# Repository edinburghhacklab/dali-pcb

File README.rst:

DALI PCB
========

Overview
--------

PCB to power and interface with DALI using an ESP32-S3.

Dimensions: 100mm W × 75mm H

Usage
-----

This is a KiCad project.

* `Software <https://github.com/edinburghhacklab/mqtt-dali-controller>`_

Schematics
----------

Power for the DALI bus is optional and can be connected using the solder jumper
bridges. If the power is supplied by this PCB then the polarity of the bus is
fixed so the bridge rectifier can be omitted.

.. image:: render/Root-sch.svg
   :alt: Root schematic

DALI
~~~~

There are 2 DALI bus connections.

.. image:: render/DALI-sch.svg
   :alt: DALI schematic

Power
~~~~~

Power for the DALI bus is supplied by an external 12-22V DC power supply. Power
for the microcontroller is supplied by USB to the development board or an
external 5V DC power supply.

.. image:: render/Power-sch.svg
   :alt: Power schematic

Microcontroller
~~~~~~~~~~~~~~~

Connect a `LOLIN S3  <https://www.wemos.cc/en/latest/s3/s3.html>`_ development
board to the pin sockets.

.. image:: render/Microcontroller-sch.svg
   :alt: Microcontroller schematic

I/O
~~~

Analogue and digital I/O pin headers are provided for integrations with external
switches and rotary encoders.

The DALI bus also has a 3.3V direct pin header which can only be used when the
microcontroller is disconnected. This can't be used with a standard UART because
the DALI communication uses Manchester (bi-phase) encoding.

.. image:: render/IO-sch.svg
   :alt: I/O schematic

PCB
---

* Internal bus power: populate JP1-2, and populate either JP3-4 or D5
* External bus power: populate D5, do not populate JP1-4

.. image:: render/DALI-pcb.svg
   :alt: DALI PCB

Components
----------

+---------------------+----------+--------------------------------------------------------+
| Refs                | Quantity | Name                                                   |
+=====================+==========+========================================================+
|                     |     1    | LOLIN S3 Development Board                             |
+---------------------+----------+--------------------------------------------------------+
| D3                  |     1    | Diodes BAV99-7-F Dual Switching Diode, SOT-23-3        |
+---------------------+----------+--------------------------------------------------------+
| D4                  |     1    | Diodes DDZ9689S-7 Zener Diode, SOD-323                 |
+---------------------+----------+--------------------------------------------------------+
| D5                  |     1    | Infineon BGX50AE6327 Diode Bridge, SOT-143             |
+---------------------+----------+--------------------------------------------------------+
| J1, J2, J3, J4      |     4    | 1x02 Terminal Block, Through Hole (5.08mm)             |
+---------------------+----------+--------------------------------------------------------+
| J5, J6              |     2    | 1x20 Pin Socket, Through Hole (2.54mm)                 |
+---------------------+----------+--------------------------------------------------------+
| J7                  |     1    | 1x04 Pin Header, Through Hole (2.54mm)                 |
+---------------------+----------+--------------------------------------------------------+
| J8, J9              |     2    | 2x13 Pin Header, Through Hole (2.54mm)                 |
+---------------------+----------+--------------------------------------------------------+
| Q1                  |     1    | ON Semiconductor PZT2222AT1G NPN Transistor, SOT-223   |
+---------------------+----------+--------------------------------------------------------+
| Q2                  |     1    | ON Semiconductor MMBT2222ALT1G NPN Transistor, SOT-23  |
+---------------------+----------+--------------------------------------------------------+
| R2                  |     1    | 12Ω 1W Resistor, SMD 2512 (Metric 6332)                |
+---------------------+----------+--------------------------------------------------------+
| R3, R8              |     2    | 1kΩ 1W Resistor, SMD 2512 (Metric 6332)                |
+---------------------+----------+--------------------------------------------------------+
| R4                  |     1    | 120Ω 125mW Resistor, SMD 0805 (Metric 2012)            |
+---------------------+----------+--------------------------------------------------------+
| R5                  |     1    | 220Ω 125mW Resistor, SMD 0805 (Metric 2012)            |
+---------------------+----------+--------------------------------------------------------+
| R6                  |     1    | 2.2kΩ 250mW Resistor, SMD 1206 (Metric 3216)           |
+---------------------+----------+--------------------------------------------------------+
| R7                  |     1    | 10kΩ 125mW Resistor, SMD 0805 (Metric 2012)            |
+---------------------+----------+--------------------------------------------------------+
| U1, U2              |     2    | Vishay Semiconductors TCLT1000 Optocoupler, SOP-4L     |
+---------------------+----------+--------------------------------------------------------+

Total pin header count: 56

References
----------

* `Digitally Addressable Lighting Interface (DALI) Communication <https://ww1.microchip.com/downloads/en/AppNotes/01465A.pdf>`_

* `Digitally Addressable Lighting Interface (DALI) Unit Using the MC68HC908KX8 <https://www.nxp.com/docs/en/reference-manual/DRM004.pdf>`_

* `Digital Addressable Lighting Interface (DALI) Implementation Using MSP430 Value Line Microcontrollers <https://www.ti.com/lit/an/slaa422a/slaa422a.pdf>`_

* `DALI Communication Using the EFR32 <https://www.silabs.com/documents/public/application-notes/an1220-efr32-dali.pdf>`_

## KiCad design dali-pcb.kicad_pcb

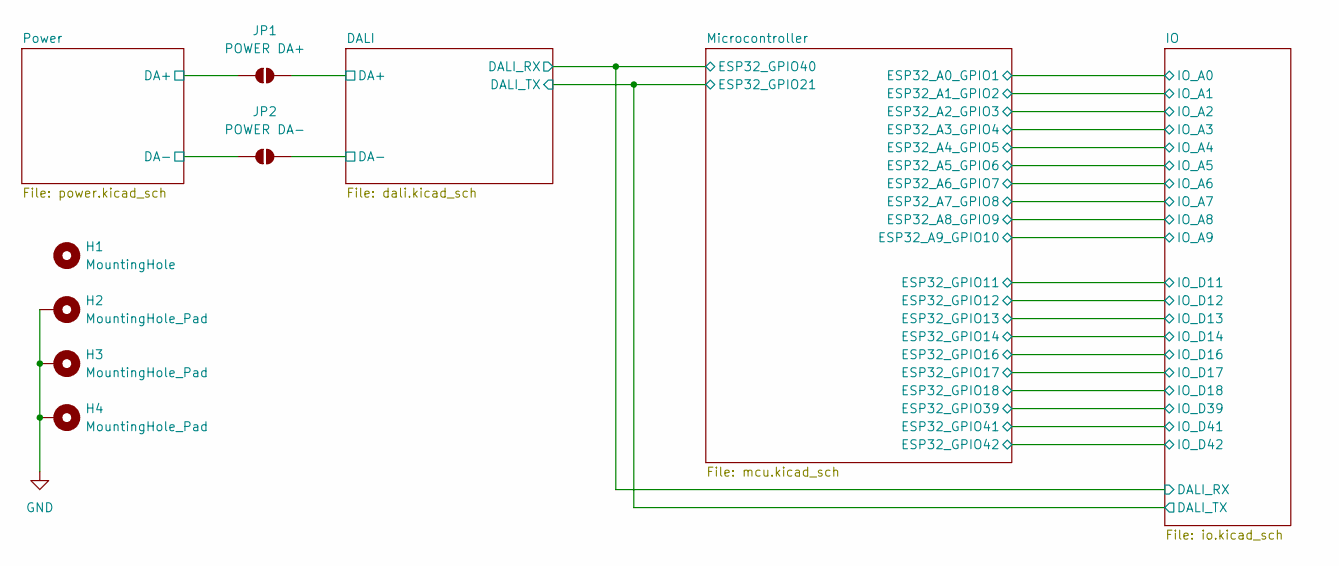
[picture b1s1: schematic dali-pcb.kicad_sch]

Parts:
H1: MountingHole; MountingHole_3.2mm_M3
H2, H3, H4: MountingHole_Pad; MountingHole_3.2mm_M3_Pad
JP1: POWER DA+; SolderJumper-2_P1.3mm_Open_RoundedPad1.0x1.5mm
JP2: POWER DA-; SolderJumper-2_P1.3mm_Open_RoundedPad1.0x1.5mm

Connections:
/DALI/DA+: JP1.1 (A); also elsewhere on the board
/DALI/DA-: JP2.2 (B); also elsewhere on the board
/Power/DA+: JP1.2 (B); also elsewhere on the board
/Power/DA-: JP2.1 (A); also elsewhere on the board
GND: H2.1, H3.1, H4.1; also elsewhere on the board

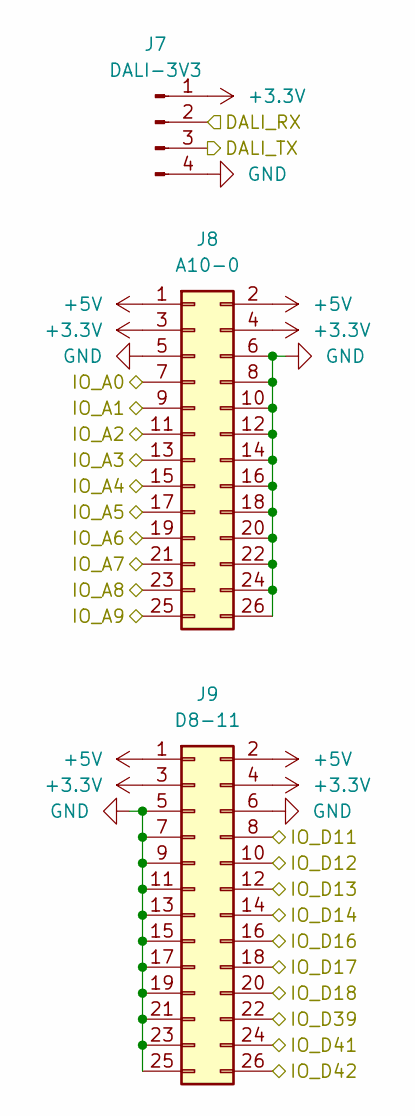
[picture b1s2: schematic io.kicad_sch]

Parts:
J7: DALI-3V3; PinHeader_1x04_P2.54mm_Vertical
J8: A10-0; PinHeader_2x13_P2.54mm_Vertical
J9: D8-11; PinHeader_2x13_P2.54mm_Vertical

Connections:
+3.3V: J7.1, J8.3, J8.4, J9.3, J9.4; also elsewhere on the board
+5V: J8.1, J8.2, J9.1, J9.2; also elsewhere on the board
/DALI/DALI_RX: J7.2; also elsewhere on the board
/DALI/DALI_TX: J7.3; also elsewhere on the board
/IO/IO_A0: J8.7; also elsewhere on the board
/IO/IO_A1: J8.9; also elsewhere on the board
/IO/IO_A2: J8.11; also elsewhere on the board
/IO/IO_A3: J8.13; also elsewhere on the board
/IO/IO_A4: J8.15; also elsewhere on the board
/IO/IO_A5: J8.17; also elsewhere on the board
/IO/IO_A6: J8.19; also elsewhere on the board
/IO/IO_A7: J8.21; also elsewhere on the board
/IO/IO_A8: J8.23; also elsewhere on the board
/IO/IO_A9: J8.25; also elsewhere on the board
/IO/IO_D11: J9.8; also elsewhere on the board
/IO/IO_D12: J9.10; also elsewhere on the board
/IO/IO_D13: J9.12; also elsewhere on the board
/IO/IO_D14: J9.14; also elsewhere on the board
/IO/IO_D16: J9.16; also elsewhere on the board
/IO/IO_D17: J9.18; also elsewhere on the board
/IO/IO_D18: J9.20; also elsewhere on the board
/IO/IO_D39: J9.22; also elsewhere on the board
/IO/IO_D41: J9.24; also elsewhere on the board
/IO/IO_D42: J9.26; also elsewhere on the board
GND: J7.4, J8.5, J8.6, J8.8, J8.10, J8.12, J8.14, J8.16, J8.18, J8.20, J8.22, J8.24, J8.26, J9.5, J9.6, J9.7, J9.9, J9.11, J9.13, J9.15, J9.17, J9.19, J9.21, J9.23, J9.25; also elsewhere on the board

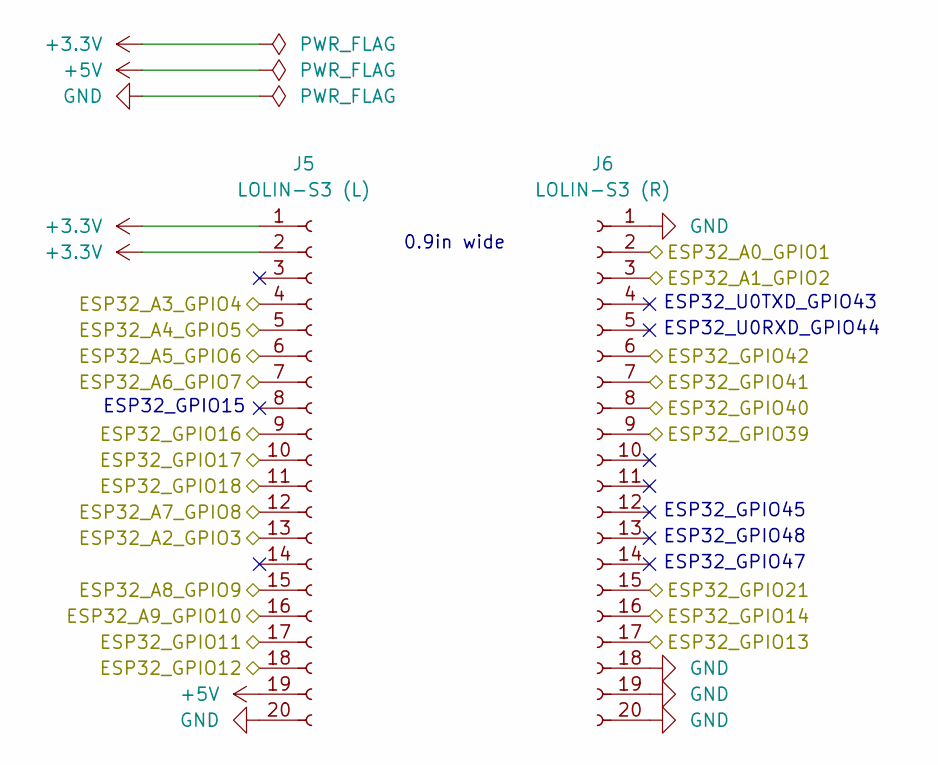
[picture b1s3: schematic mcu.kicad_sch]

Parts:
J5: LOLIN-S3 (L); PinSocket_1x20_P2.54mm_Vertical
J6: LOLIN-S3 (R); PinSocket_1x20_P2.54mm_Vertical

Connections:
+3.3V: J5.1, J5.2; also elsewhere on the board
+5V: J5.19; also elsewhere on the board
/DALI/DALI_RX: J6.8; also elsewhere on the board
/DALI/DALI_TX: J6.15; also elsewhere on the board
/IO/IO_A0: J6.2; also elsewhere on the board
/IO/IO_A1: J6.3; also elsewhere on the board
/IO/IO_A2: J5.13; also elsewhere on the board
/IO/IO_A3: J5.4; also elsewhere on the board
/IO/IO_A4: J5.5; also elsewhere on the board
/IO/IO_A5: J5.6; also elsewhere on the board
/IO/IO_A6: J5.7; also elsewhere on the board
/IO/IO_A7: J5.12; also elsewhere on the board
/IO/IO_A8: J5.15; also elsewhere on the board
/IO/IO_A9: J5.16; also elsewhere on the board
/IO/IO_D11: J5.17; also elsewhere on the board
/IO/IO_D12: J5.18; also elsewhere on the board
/IO/IO_D13: J6.17; also elsewhere on the board
/IO/IO_D14: J6.16; also elsewhere on the board
/IO/IO_D16: J5.9; also elsewhere on the board
/IO/IO_D17: J5.10; also elsewhere on the board
/IO/IO_D18: J5.11; also elsewhere on the board
/IO/IO_D39: J6.9; also elsewhere on the board
/IO/IO_D41: J6.7; also elsewhere on the board
/IO/IO_D42: J6.6; also elsewhere on the board
GND: J5.20, J6.1, J6.18, J6.19, J6.20; also elsewhere on the board

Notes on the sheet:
ESP32_U0TXD_GPIO43
ESP32_GPIO15
0.9in wide
ESP32_GPIO47
ESP32_GPIO45
ESP32_GPIO48
ESP32_U0RXD_GPIO44

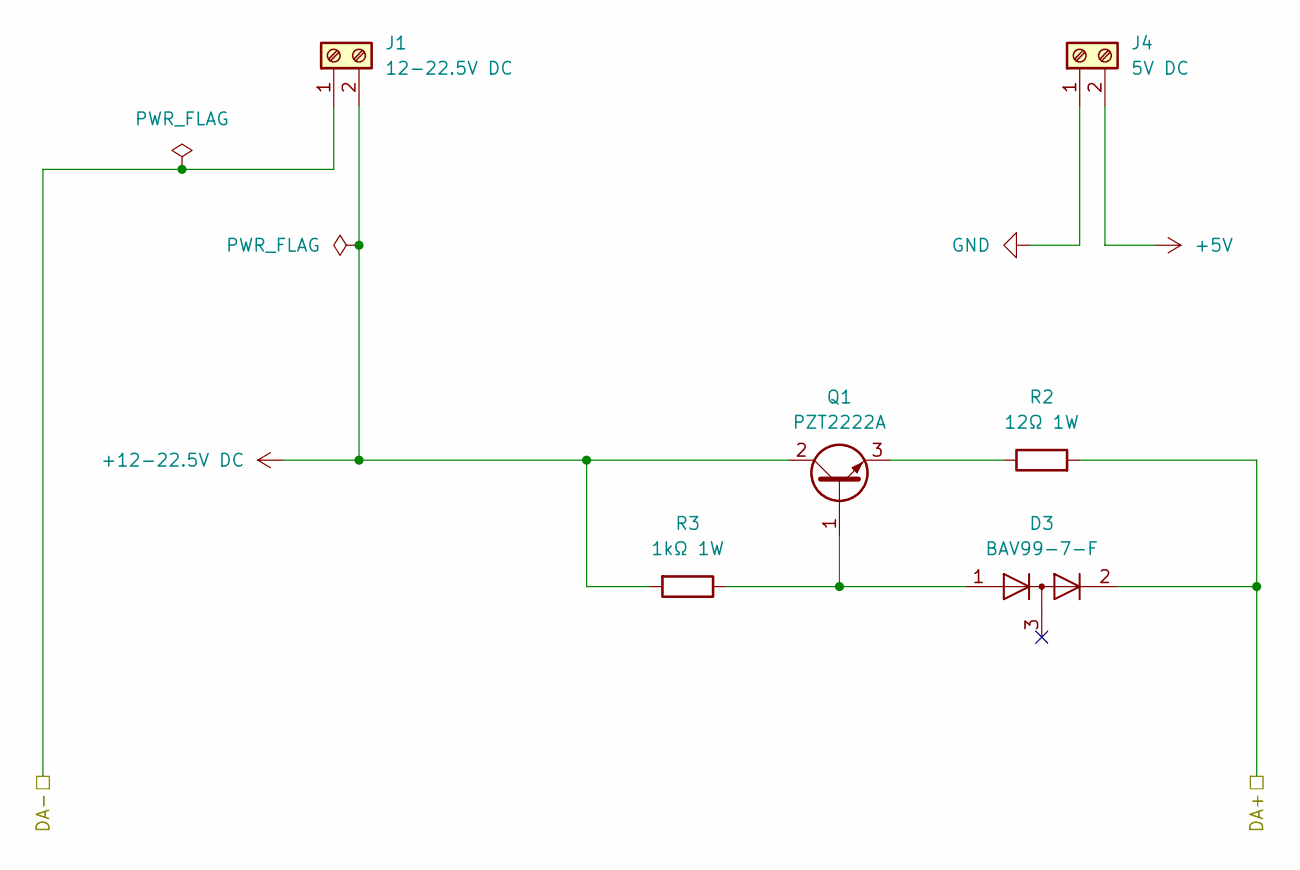
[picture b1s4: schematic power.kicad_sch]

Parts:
D3: BAV99-7-F; SOT-23_Handsoldering
J1: 12-22.5V DC; TerminalBlock_bornier-2_P5.08mm
J4: 5V DC; TerminalBlock_bornier-2_P5.08mm
Q1: PZT2222A; SOT-223-3_TabPin2
R2: 12Ω 1W; R_2512_6332Metric_Pad1.40x3.35mm_HandSolder
R3: 1kΩ 1W; R_2512_6332Metric_Pad1.40x3.35mm_HandSolder

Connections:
+5V: J4.2; also elsewhere on the board
+12-22.5V DC: J1.2, Q1.2 (C), R3.2
/Power/DA+: D3.2 (A), R2.2; also elsewhere on the board
/Power/DA-: J1.1; also elsewhere on the board
GND: J4.1; also elsewhere on the board
unnamed: D3.1 (K), Q1.1 (B), R3.1
unnamed: Q1.3 (E), R2.1

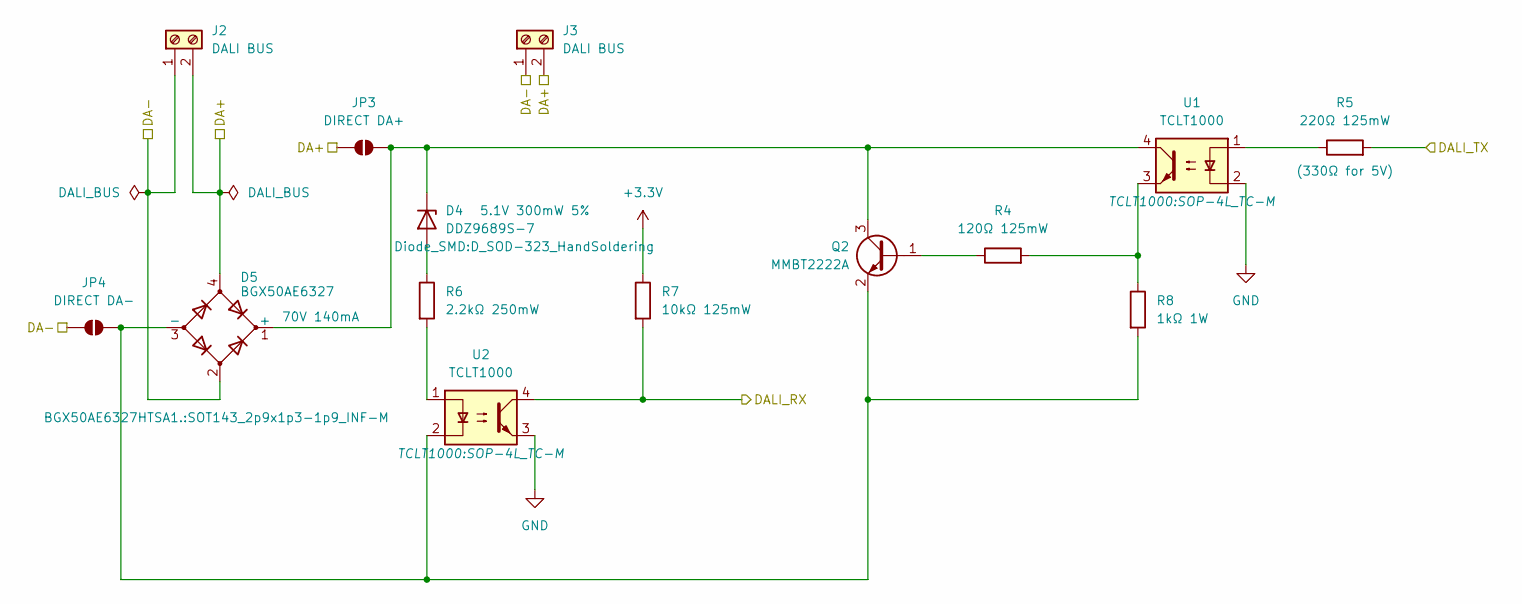
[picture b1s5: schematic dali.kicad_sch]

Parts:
D4: DDZ9689S-7; D_SOD-323_HandSoldering
D5: BGX50AE6327; SOT143_2p9x1p3-1p9_INF-M
J2, J3: DALI BUS; TerminalBlock_bornier-2_P5.08mm
JP3: DIRECT DA+; SolderJumper-2_P1.3mm_Open_RoundedPad1.0x1.5mm
JP4: DIRECT DA-; SolderJumper-2_P1.3mm_Open_RoundedPad1.0x1.5mm
Q2: MMBT2222A; SOT-23_Handsoldering
R4: 120Ω 125mW; R_0805_2012Metric_Pad1.20x1.40mm_HandSolder
R5: 220Ω 125mW; R_0805_2012Metric_Pad1.20x1.40mm_HandSolder
R6: 2.2kΩ 250mW; R_1206_3216Metric_Pad1.30x1.75mm_HandSolder
R7: 10kΩ 125mW; R_0805_2012Metric_Pad1.20x1.40mm_HandSolder
R8: 1kΩ 1W; R_2512_6332Metric_Pad1.40x3.35mm_HandSolder
U1, U2: TCLT1000; SOP-4L_TC-M

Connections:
+3.3V: R7.1; also elsewhere on the board
/DALI/DA+: D5.4, J2.2, J3.2, JP3.2 (B); also elsewhere on the board
/DALI/DA-: D5.2, J2.1, J3.1, JP4.2 (B); also elsewhere on the board
/DALI/DALI_RX: R7.2, U2.4; also elsewhere on the board
/DALI/DALI_TX: R5.2; also elsewhere on the board
GND: U1.2, U2.3; also elsewhere on the board
unnamed: D4.2 (A), R6.1
unnamed: D4.1 (K), D5.1 (+), JP3.1 (A), Q2.3 (C), U1.4
unnamed: D5.3 (-), JP4.1 (A), Q2.2 (E), R8.2, U2.2
unnamed: Q2.1 (B), R4.1
unnamed: R4.2, R8.1, U1.3
unnamed: R5.1, U1.1
unnamed: R6.2, U2.1

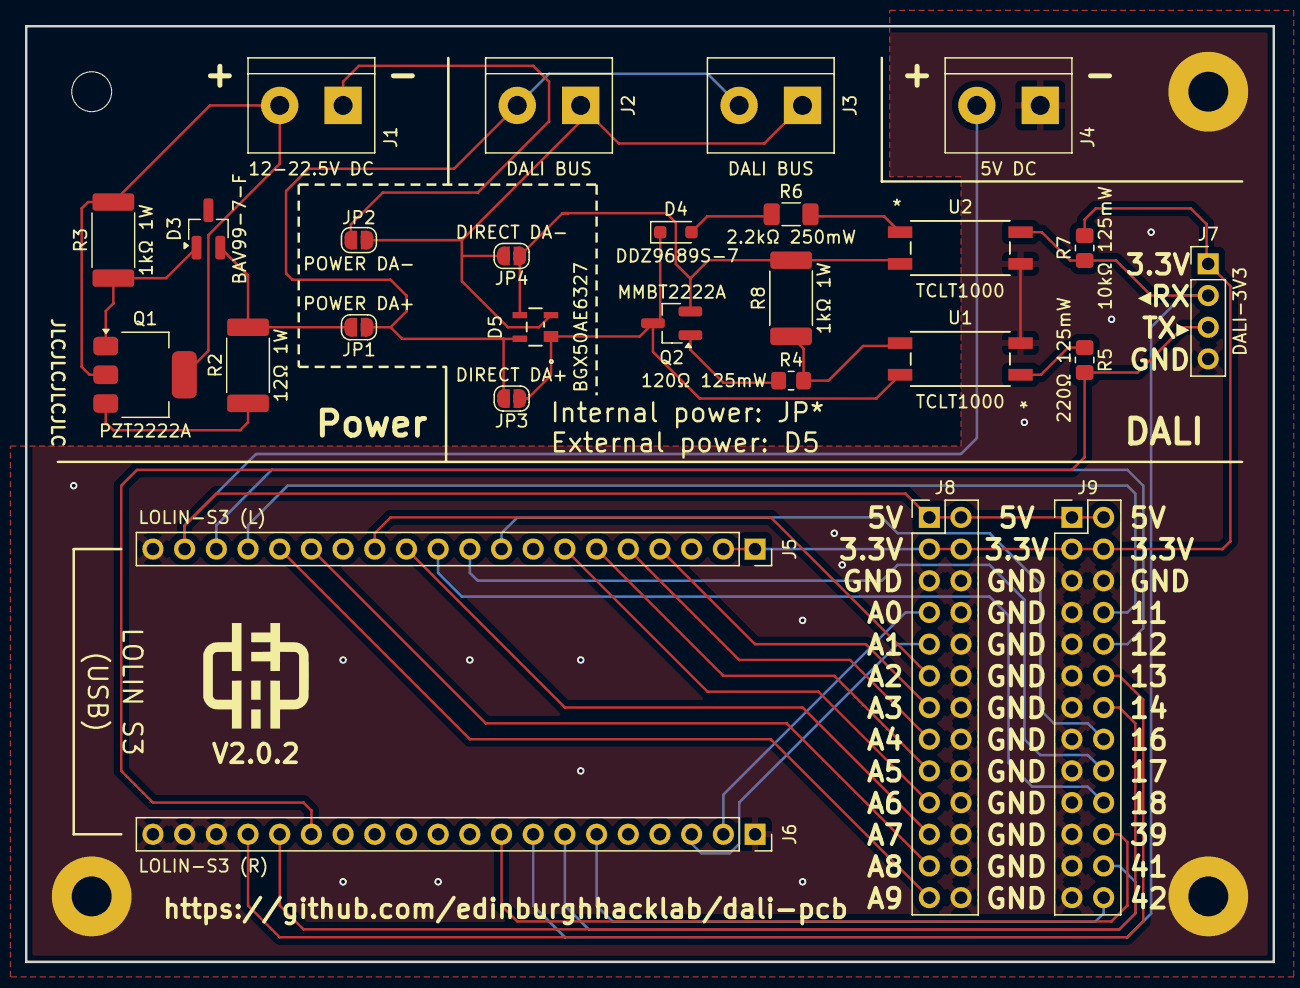
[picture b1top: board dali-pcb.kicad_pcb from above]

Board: 2 copper layers, 100.0 x 75.0 mm, 32 parts (0 on the bottom side), 39 nets.

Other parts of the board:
EHLAB: LOGO

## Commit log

2025-07-08 Swap the order of the FTDI data pins
2025-07-08 Rename UART pins to use Espressif convention
2025-07-08 The microcontroller can also be powered using USB
2025-07-08 Add an FTDI connector for the DALI bus
2025-07-08 Note support for FTDI TTL-232R-3V3 in the overview
2025-07-08 Connect 5V from the FTDI connector to the DALI comms circuit
2025-07-08 Add individual two-pin switch I/O headers
2025-07-08 Assign footprints to resistors and use solder jumpers
2025-07-08 Assign footprints for the remaining components
2025-07-08 Update schematic for 3.3V and specify resistor power
2025-07-08 Place all components
2025-07-08 Increase board size to protect the MCU USB connections
2025-07-08 Add +/- labels to screw terminals
2025-07-09 FTDI TTL-232R-3V3 can't be used to directly interface with DALI
    There's no 3.3V supply to use as a pull-up
2025-07-09 Rotate R3 and improve silkscreen positions
2025-07-09 Add LOLIN S3 mini support
2025-07-09 Renumber references and place LOLIN-S3-MINI
2025-07-09 Add logo, URLs, version
2025-07-09 Render PCB
2025-07-09 Move LOLIN mini boards further away from FTDI/UART pin headers
2025-07-09 Don't connect unused GPIOs together across MCUs
2025-07-09 Label all the I/O pins
2025-07-09 Fix screw terminal orientation and mounting holes
2025-07-09 Add easy MCU traces and all the analogue I/O internal traces
2025-07-09 First routing attempt
2025-07-09 Swap order of microcontrollers to avoid a mess of tracks
2025-07-09 Second routing attempt
2025-07-09 Everything is now connected
2025-07-10 Add more vias to reduce GND islands
2025-07-10 Add solder jumpers to bypass the bridge rectifier
2025-07-10 Reduce root schematic page size
2025-07-10 Move power instructions to the PCB section
2025-07-10 Add more silkscreen to explain where things are
2025-07-10 Fix ESP32-S3-DEVKITC-1 bottom right pins
2025-07-10 Check and list components
2025-07-10 Move D5/JP3/JP4 to improve silkscreen position
2025-07-10 Reword bus power options
2025-07-10 Add JLC text
2025-07-11 Remove the kitchen sink
2025-07-11 Add Gerber files for JLCPCB
2025-07-11 Update Gerber files for JLCPCB
2025-07-11 Fix indirect track route from Q2 to R8 via U2
2025-07-11 Fix pin header count
2025-07-11 Fix indirect track route from JP4 to R8 via Q2
2025-07-11 Move J7 further away from the edge of the PCB and realign R5/R7
2025-07-11 Show distance between bottom edge of PCB and I/O pin headers
2025-07-11 Fix other measurement positions
2025-07-11 Rename the UART connection to DIRECT because it needs Manchester encoding
2025-07-11 Avoid using the name "DIRECT" in two places with different meanings
2025-07-12 Remove dash
2025-07-12 Restore missing tracks
2025-07-12 Tidy up DALI_TX connection
2025-07-13 Add 3D models for D5, U1 and U2
2025-07-16 Remove connection between J1 (1) and GND
2025-07-16 Remove filled GND zone from under the DALI power/bus components
2025-08-07 Add reference document
2025-08-07 Link to software
